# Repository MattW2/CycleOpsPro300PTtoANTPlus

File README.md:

# CycleOpsPro300PTtoANTPlus
Read in the raw data from the CycleOps Pro 300PT Indoor Cycle wheel and output it as a ANT+ signal using an Arduino and Nordic nRF24AP

## Background
I got a really good deal on Craigslist on this indoor bike. I had also recently become addicted to Zwift and really wanted to be able to use this with Zwift rather than use my bike on a trainer. The included computer refused to save data past about 10 minutes making it all but worthless for saving training sessions. As I find time I'll be documenting the reverse engineering and build at [https://www.blinkyme.com/](https://www.blinkyme.com/) see website for project details

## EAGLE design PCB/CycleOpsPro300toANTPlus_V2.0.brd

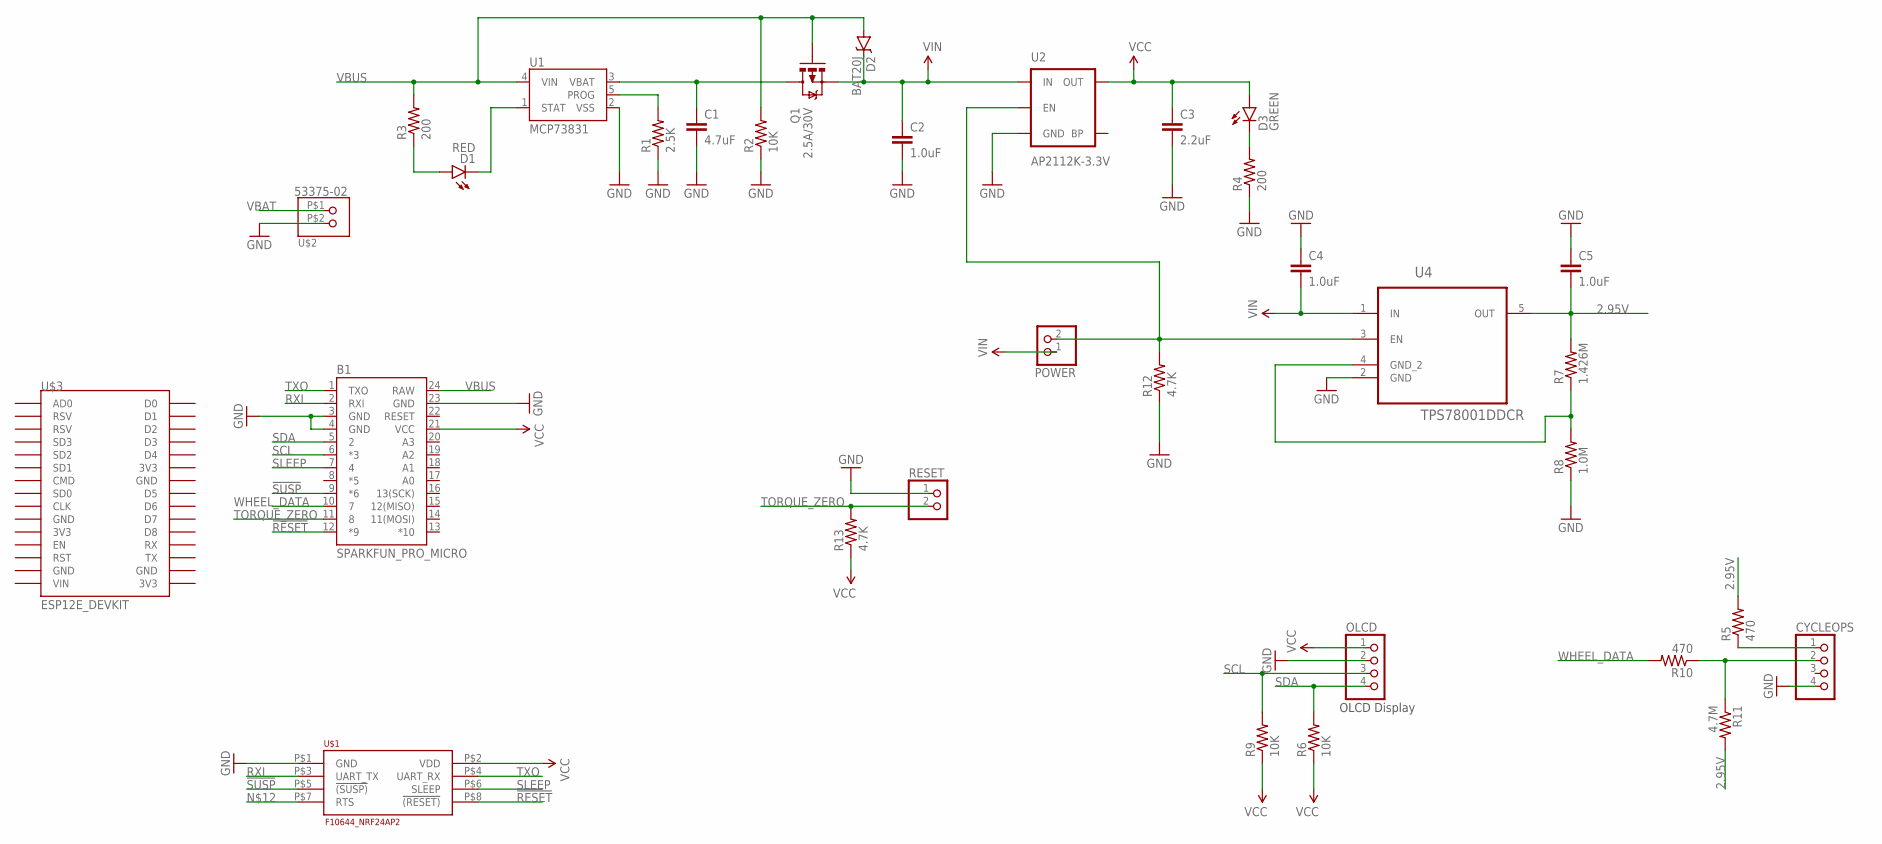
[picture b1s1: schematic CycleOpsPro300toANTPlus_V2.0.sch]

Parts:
B1: SPARKFUN_PRO_MICRO
C1: 4.7uF; 0603-CAP
C2, C4, C5: 1.0uF; 0603-CAP
C3: 2.2uF; 0603-CAP
CYCLEOPS: PINHD-1X4; 1X04
D1: RED; LED-0603
D2: BAT20J; SOD-323
D3: GREEN; LED-0603
OLCD: PINHD-1X4; 1X04
POWER: PINHD-1X2; 1X02
Q1: 2.5A/30V; SOT23-3
R1: 2.5K; 0603-RES
R2, R6, R9: 10K; 0603-RES
R3, R4: 200; 0603-RES
R5, R10: 470; 0603-RES
R7: 1.426M; 0603-RES
R8: 1.0M; 0603-RES
R11: 4.7M; 0603-RES
R12, R13: 4.7K; 0603-RES
RESET: PINHD-1X2; 1X02
U1: MCP73831; SOT23-5
U2: AP2112K-3.3V; SOT23-5
U4: TPS78001DDCR; SOT95P280X110-5N
U$1: F10644_NRF24AP2
U$2: 53375-02
U$3: ESP12E_DEVKIT

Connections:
2.95V: C5.2, R5.2, R7.2, R11.2, U4.5 (OUT)
!RESET: B1.12 (*9), U$1.P$8 (!(RESET))
!SUSP: B1.9 (*6), U$1.P$5 (!(SUSP))
GND: B1.3 (GND), B1.4 (GND), B1.23 (GND), C1.2, C2.2, C3.2, C4.1, C5.1, CYCLEOPS.4, OLCD.2, R1.1, R2.1, R4.1, R8.1, R12.1, RESET.1, U1.2 (VSS), U2.2 (GND), U4.2 (GND), U$1.P$1 (GND), U$2.P$2
unnamed: D1.A, R3.1
unnamed: D1.C, U1.1 (STAT)
unnamed: CYCLEOPS.1, R5.1
unnamed: R1.2, U1.5 (PROG)
unnamed: CYCLEOPS.2, R10.1, R11.1
unnamed: D3.C, R4.2
unnamed: POWER.2, R12.2, U2.3 (EN), U4.3 (EN)
unnamed: R7.1, R8.2, U4.4 (GND_2)
RXI: B1.2 (RXI), U$1.P$3 (UART_TX)
SCL: B1.6 (*3), OLCD.3, R9.2
SDA: B1.5 (2), OLCD.4, R6.2
SLEEP: B1.7 (4), U$1.P$6 (SLEEP)
TORQUE_ZERO: B1.11 (8), R13.2, RESET.2
TXO: B1.1 (TXO), U$1.P$4 (UART_RX)
VBAT: C1.1, Q1.3 (D), U1.3 (VBAT), U$2.P$1
VBUS: B1.24 (RAW), D2.A, Q1.1 (G), R2.2, R3.2, U1.4 (VIN)
VCC: B1.21 (VCC), C3.1, D3.A, OLCD.1, R6.1, R9.1, R13.1, U2.5 (OUT), U$1.P$2 (VDD)
VIN: C2.1, C4.2, D2.C, POWER.1, Q1.2 (S), U2.1 (IN), U4.1 (IN)
WHEEL_DATA: B1.10 (7), R10.2

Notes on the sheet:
OLCD Display

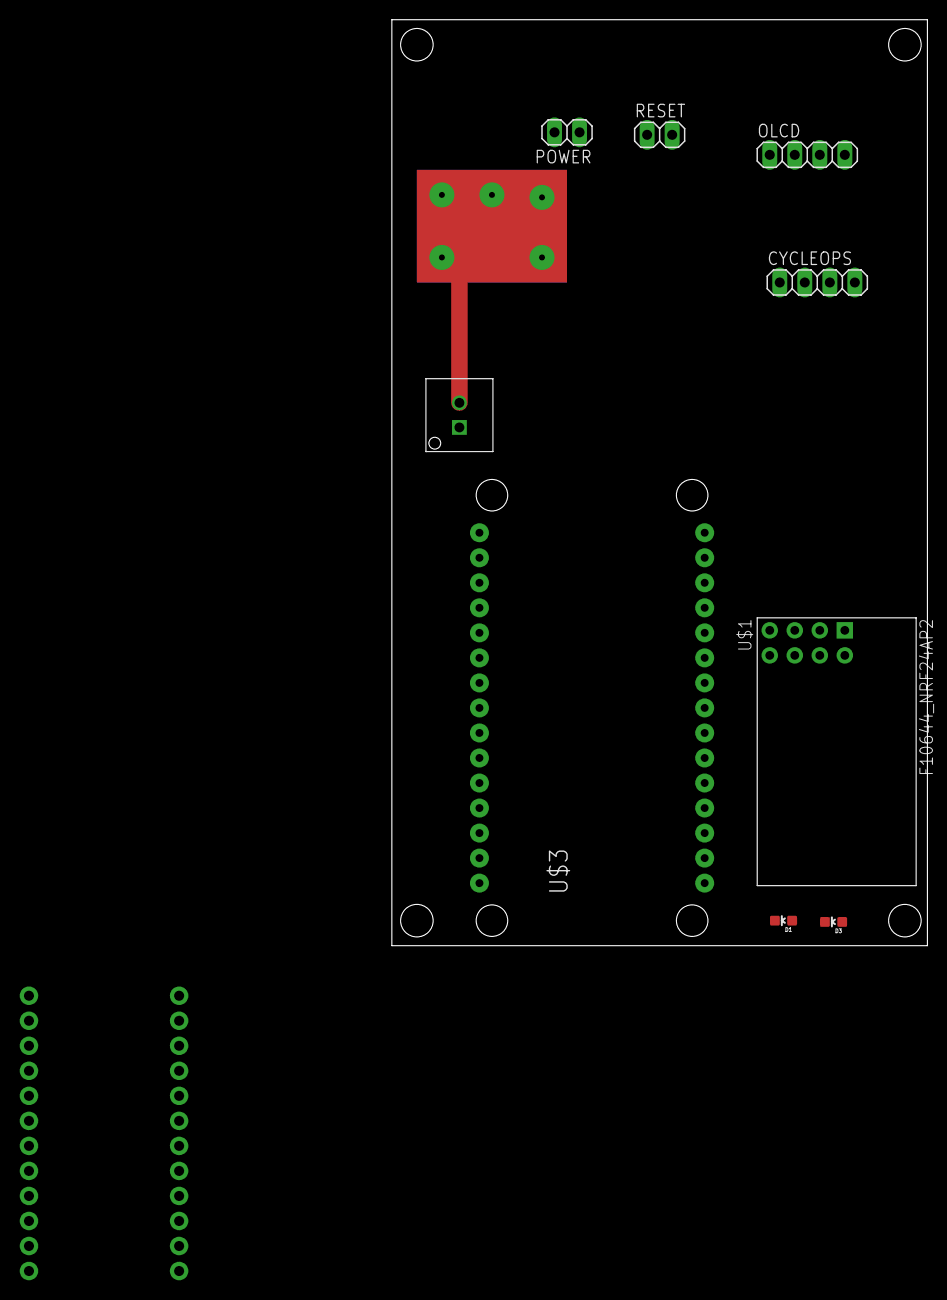
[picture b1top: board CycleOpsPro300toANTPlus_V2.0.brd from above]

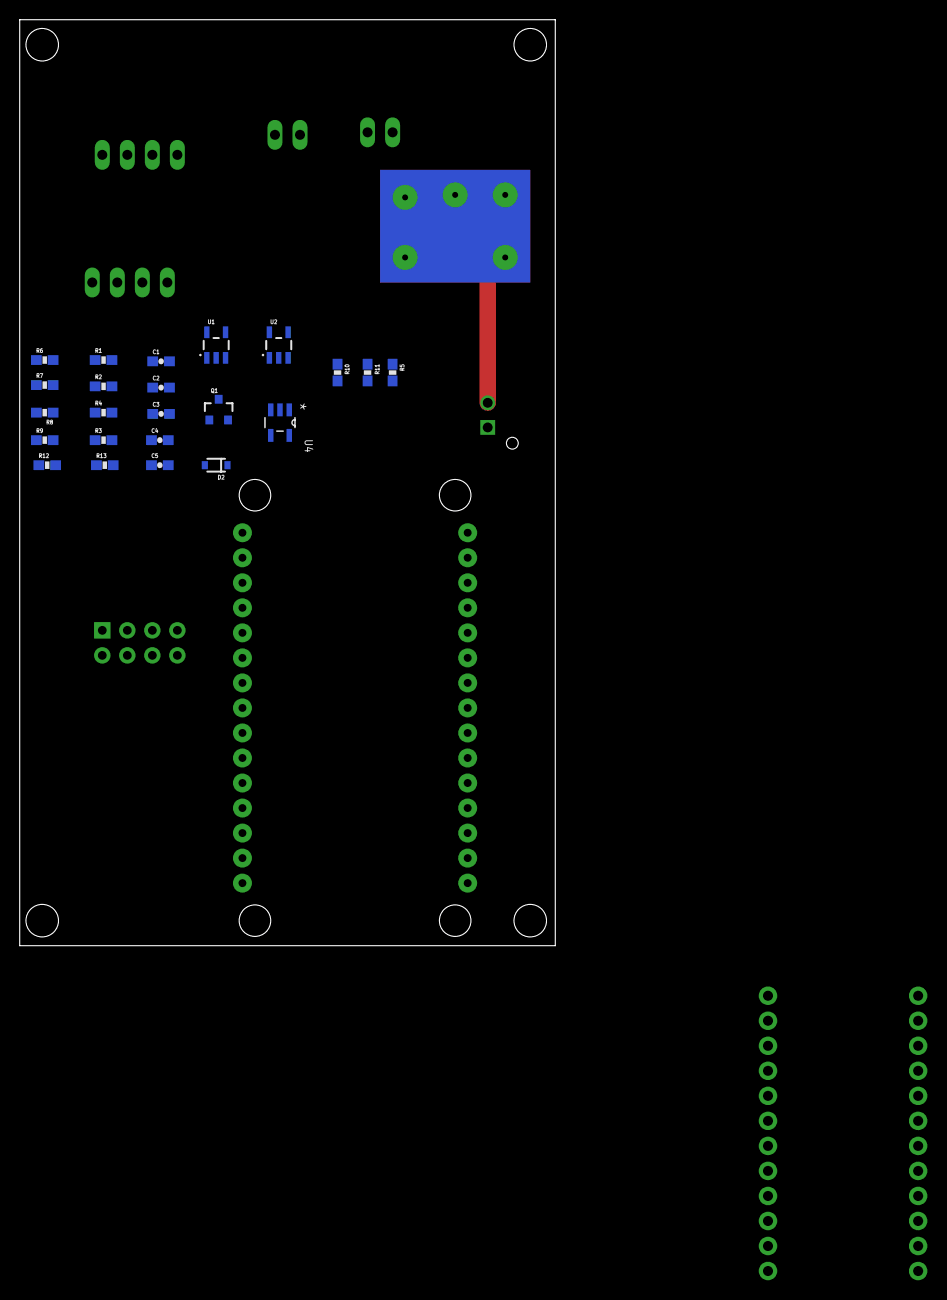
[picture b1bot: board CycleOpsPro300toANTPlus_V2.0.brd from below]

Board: 2 copper layers, 54.4 x 94.0 mm, 33 parts (23 on the bottom side), 23 nets.

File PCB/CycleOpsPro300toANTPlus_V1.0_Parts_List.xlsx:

Part | Value | Package | Description | Mouser Part # | Link | Device | Cost
B1 | PRO MICRO | SPARKFUN_PRO_MICRO | SparkFun Pro Micro |  | http://www.ebay.com/itm/Leonardo-Pro-Micro-ATmega32U4-8MHz-3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 | SPARKFUN_PRO_MICRO | 8.73
Battery 14500 3.7V Li-Ion |  |  |  |  | http://www.dx.com/p/trustfire-protected-14500-3-7v-900mah-li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 |  | 2.8650000000000002
C1 | 4.7uF | 0603-CAP | Capacitor | 581-06036D475MAT4A |  | CAP0603-CAP | 0.22
C2, C4, C5 | 1.0uF | 0603-CAP | Capacitor | 581-06036D105MAT2A |  | CAP0603-CAP | 0.11
C3 | 2.2uF | 0603-CAP | Capacitor | 581-06036D225MAT2A |  | CAP0603-CAP | 0.17
D1 | RED | LED-0603 | LEDs | 645-598-8010-107F |  | LED0603 | 0.45
D2 | BAT20J | SOD-323 | Schottky diodes in SFE's production catalog | 511-BAT20JFILM |  | DIODE-SCHOTTKY-BAT20J
D3 | GREEN | LED-0603 | LEDs | 645-598-8070-107F |  | LED0603 | 0.45
Molex Micro-Fit 4 Circuit plug Housing |  |  |  | 538-43020-0400 |  |  | 0.38
Molex Micro-Fit Pins |  |  |  | 538-43031-0007 |  |  | 0.92
OLED Display |  |  |  |  | http://www.ebay.com/itm/191785893008?_trksid=p2057872.m2749.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 |  | 11.95
Power Switch |  | Mountain Switch | Toggle Switches SPST OFF-ON | 108-0041-EVX |  | 108-0041-EVX | 2.83
Project Case |  |  |  |  | http://www.ebay.com/itm/5-PCS-Plastic-Instrument-Case-Electr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 |  | 0.9
Q1 | 2.5A/30V | SOT23-3 | Generic PMOSFET | 621-DMG2307L-7 |  | MOSFET-PCHANNELDMG2307L
R1 | 2.49K | 0603-RES | Resistor | 660-RK73H1JTTD2491F |  | RESISTOR0603-RES
R11 | 4.7M | 0603-RES | Resistor | 660-RK73B1JTTDD475J |  | RESISTOR0603-RES
R12, R13 | 4.7K | 0603-RES | Resistor | 667-ERJ-3GEYJ472V |  | RESISTOR0603-RES
R2, R6, R9 | 10K | 0603-RES | Resistor | 660-RK73H1JTTD1002F |  | RESISTOR0603-RES
R3, R4 | 200 | 0603-RES | Resistor | 660-RK73H1JTTD2000F |  | RESISTOR0603-RES
R5, R10 | 470 | 0603-RES | Resistor | 660-RK73H1JTTD4700F |  | RESISTOR0603-RES
R7 | 1.43M | 0603-RES | Resistor | 71-CRCW06031M43FKEA |  | RESISTOR0603-RES
R8 | 1.0M | 0603-RES | Resistor | 652-CR0603FX-1004ELF |  | RESISTOR0603-RES
Reset Switch |  | Mountain Switch | Pushbutton Switches METAL BODY BLK | 103-1013-EVX |  | 103-1013-EVX | 1.85
U$1 | NRF24AP2 |  | NRF24AP2 Networking Module |  | https://www.aliexpress.com/snapshot/0.html?orderId=82384771664494 | F10644_NRF24AP2 | 15.6
U$2 | 53375-02 | 53375-02 | 2.50MM 2P VERT HDR FRCTN POS LOCK | 538-53375-0210 |  | 53375-02 | 0.43
U1 | MCP73831 | SOT23-5 | Charge management controller | 579-MCP73831T-2ACIOT |  | MCP73831 | 0.6
U2 | AP2112K-3.3V | SOT23-5 | Voltage Regulator LDO | 621-AP2112K-3.3TRG1 |  | V_REG_LDOSMD | 0.47
U4 | TPS78001DDCR | SOT95P280X110-5N | Low-Dropout Linear Regulator | 595-TPS78001DDCR |  | TPS78223DDCR | 1
 |  |  |  |  |  | Total | 49.924999999999997

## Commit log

2016-12-13 First Commit
    Arduino Code, working but needs cleanup
2016-12-13 Update README.md
    writing a story about where this came from
2017-01-15 Removed ANT+ key from code
2017-01-29 Change website
2017-02-26 Support for OLED Display
    Major changes to code to output power, torue and cadence to OLCD
    display. Much code cleanup
2017-02-26 Added PCB Design
2017-03-05 Updated PCB design and placed order for PCBs
2017-04-09 Added CAD Model and Partslist
2017-04-09 Updated Parts List
2017-04-16 Update to Parts List
2018-01-13 Added in error checking to the Cycleops received packet
2018-01-20 Updated CAD Model. Minor corrections to schematic. Updated BOM Parts List.
2018-04-29 Some minor changes to save memory
2018-04-30 Folder restructure, getting ready for V2 design
2018-04-30 Removed a file
2018-04-30 Fixed a file name
2018-05-13 Added a fork for ESP8266
2018-12-24 Switched to low memeory usage OLED library
2018-12-24 Cleaned up the display and fixed a flashing during update
2018-12-24 Working Read_CycleOps_V3_Power_V2_ESP8266/Read_CycleOps_V3_Power_V2_ESP8266.ino But work has stopped for now to work on new library
2018-12-24 White space cleanup
2018-12-24 Bug found in the start data bit code, cleaned up ugly comparison method with the memcmp function. Still getting some current spikes. Going to do some more work looking at clock signal.
2018-12-24 Update Read_CycleOps_V3_Power_V1.ino
    Some minor code cleanup and added a check for torque jumps. This is to stop toque spikes that look to be electrical noise from the hub itself.
2018-12-27 Update Read_CycleOps_V3_Power_V1.ino
    Convered the 6 small delay for a dead zone to a single delay. Added a function to read the checksum but still don't have a way to decode and check it.
2019-01-02 Added volatile qualifier for interrupts
    Added volatile qualifier for interrupts
2019-01-02 Look for bad bits
    First attempt at adding a bad bit detection
2019-01-02 bug fix
2019-01-05 Added real error bit detection
    Added feature to look for short pulses during the reading of data bits.
2019-01-05 Code Cleanup
    removed unused variables and some unused comments
2021-10-17 Added Speed Output
    New branch of ANT+ code that now outputs speed by adding data page 0x11
2021-10-17 Code Cleanup
    Merged in added speed output with original code branch.
2021-12-05 Corrected Wheel Circumference
    Corrected the wheel circumference such that the real bike wheel rotational velocity matches the virtual wheel such that speed and power are calculated correctly.

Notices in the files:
parts and their libraries:
SparkFun-PowerIC: Licensing: Creative Commons ShareAlike 4.0 International - https://creativecommons.org/licenses/by-sa/4.0
